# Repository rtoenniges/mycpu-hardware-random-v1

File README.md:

# MyCPU_HDW_RandomV1
A hardware random number generator for the [MyCPU](http://www.mycpu.eu/) based on the work of [Aaron Logue](http://www.cryogenius.com/hardware/rng/).

## Applications
* Games
* Math programs
* Encryption

## Features
* Address selectable through jumpers
* Two independent noise generators
* Both noise generators were adjustable through trimmers (For justage please use this [software](/hist_prg))
* Generates 2x 16bit random numbers simultaneously
* Fetch frequenz about 1MHz (means a new random number every ~16µs)

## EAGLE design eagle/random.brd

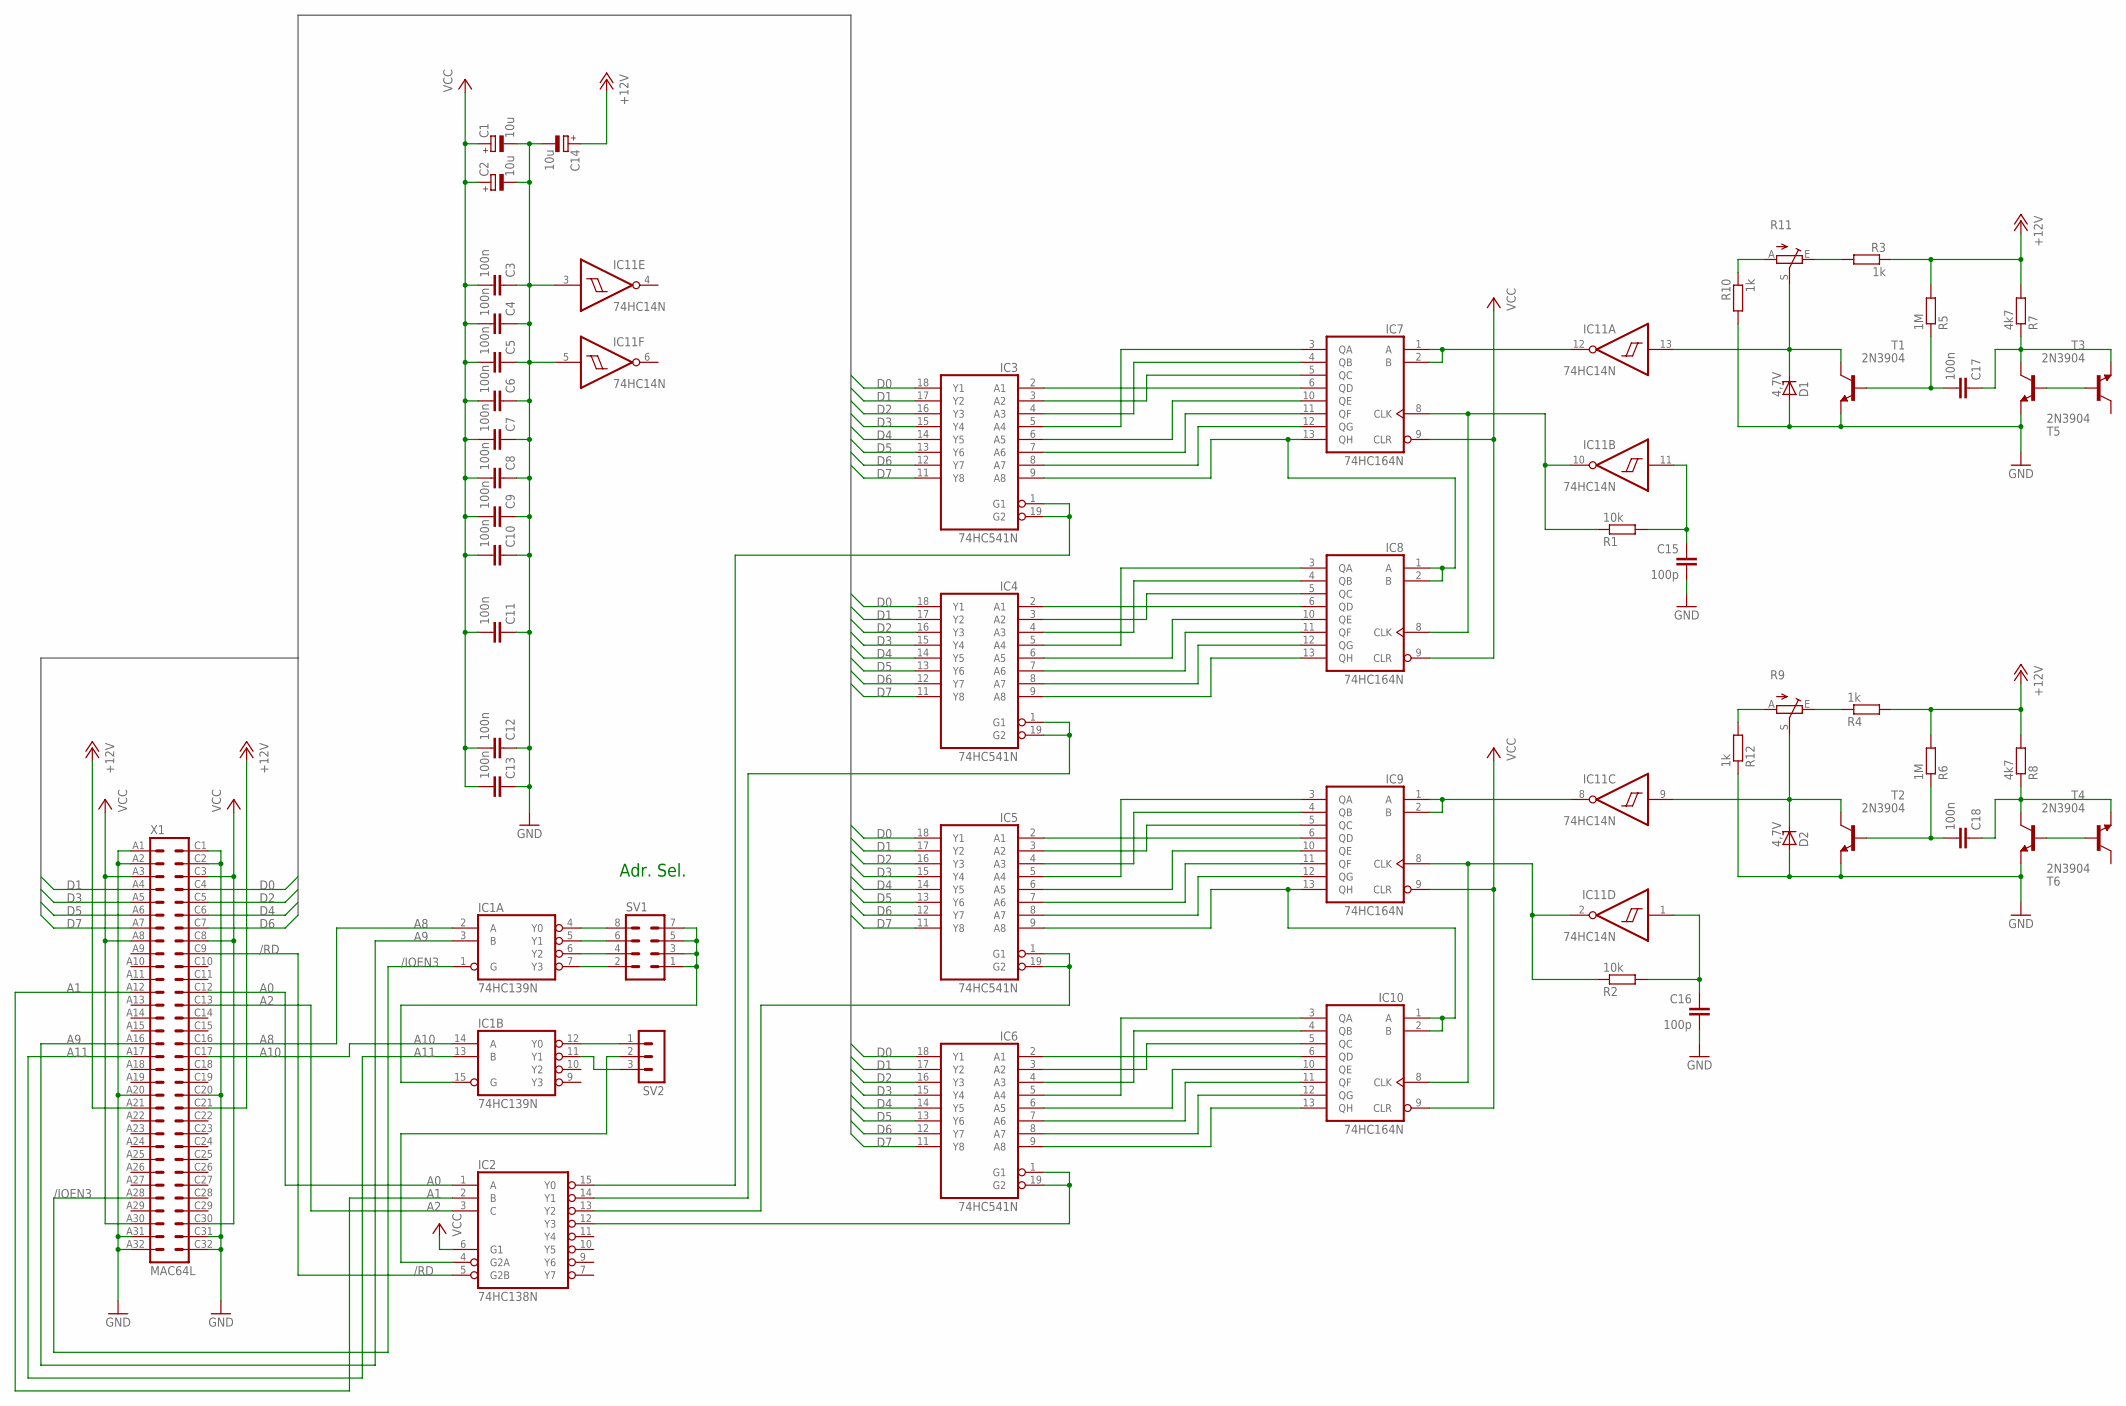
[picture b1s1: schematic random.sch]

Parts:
C1, C2, C14: 10u; TT2D4
C3, C4, C5, C6, C7, C8, C9, C10, C11, C12, C13, C17, C18: 100n; C025-024X044
C15, C16: 100p; C025-024X044
D1, D2: 4,7V; ZDIO-7.5
IC1: 74HC139N; DIL16
IC2: 74HC138N; DIL16
IC3, IC4, IC5, IC6: 74HC541N; DIL20
IC7, IC8, IC9, IC10: 74HC164N; DIL14
IC11: 74HC14N; DIL14
R1, R2: 10k; 0204/7
R3, R4, R10, R12: 1k; 0204/7
R5, R6: 1M; 0204/7
R7, R8: 4k7; 0204/7
R9, R11: TRIM_EU-S63X; S63X
SV1: MA04-2
SV2: MA03-1
T1, T2, T3, T4, T5, T6: 2N3904; TO92
X1: MAC64L

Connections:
+12V: C14.+, R3.1, R4.2, R5.2, R6.2, R7.2, R8.2, X1.A21, X1.C21
/IOEN3: IC1.1 (G), X1.A28
/RD: IC2.5 (G2B), X1.C9
A0: IC2.1 (A), X1.C12
A1: IC2.2 (B), X1.A12
A2: IC2.3 (C), X1.C13
A8: IC1.2 (A), X1.C16
A9: IC1.3 (B), X1.A16
A10: IC1.14 (A), X1.C17
A11: IC1.13 (B), X1.A17
D0: IC3.18 (Y1), IC4.18 (Y1), IC5.18 (Y1), IC6.18 (Y1), X1.C4
D1: IC3.17 (Y2), IC4.17 (Y2), IC5.17 (Y2), IC6.17 (Y2), X1.A4
D2: IC3.16 (Y3), IC4.16 (Y3), IC5.16 (Y3), IC6.16 (Y3), X1.C5
D3: IC3.15 (Y4), IC4.15 (Y4), IC5.15 (Y4), IC6.15 (Y4), X1.A5
D4: IC3.14 (Y5), IC4.14 (Y5), IC5.14 (Y5), IC6.14 (Y5), X1.C6
D5: IC3.13 (Y6), IC4.13 (Y6), IC5.13 (Y6), IC6.13 (Y6), X1.A6
D6: IC3.12 (Y7), IC4.12 (Y7), IC5.12 (Y7), IC6.12 (Y7), X1.C7
D7: IC3.11 (Y8), IC4.11 (Y8), IC5.11 (Y8), IC6.11 (Y8), X1.A7
GND: C1.-, C2.-, C3.1, C4.1, C5.1, C6.1, C7.1, C8.1, C9.1, C10.1, C11.1, C12.1, C13.1, C14.-, C15.2, C16.2, D1.A, D2.A, IC1.8 (GND), IC2.8 (GND), IC3.10 (GND), IC4.10 (GND), IC5.10 (GND), IC6.10 (GND), IC7.7 (GND), IC8.7 (GND), IC9.7 (GND), IC10.7 (GND), IC11.3 (I), IC11.5 (I), IC11.7 (GND), R10.2, R12.1, T1.3 (E), T2.3 (E), T3.3 (E), T4.3 (E), X1.A1, X1.A2, X1.A20, X1.A31, X1.A32, X1.C1, X1.C2, X1.C20, X1.C31, X1.C32
unnamed: T3.2 (B), T5.2 (B)
unnamed: C17.1, R7.1, T3.1 (C), T5.3 (E)
unnamed: C17.2, R5.1, T1.2 (B)
unnamed: D1.C, IC11.13 (I), R11.S, T1.1 (C)
unnamed: T4.2 (B), T6.2 (B)
unnamed: C18.1, R8.1, T4.1 (C), T6.3 (E)
unnamed: C18.2, R6.1, T2.2 (B)
unnamed: D2.C, IC11.9 (I), R9.S, T2.1 (C)
unnamed: C16.1, IC11.1 (I), R2.2
unnamed: IC7.8 (CLK), IC8.8 (CLK), IC11.10 (O), R1.1
unnamed: C15.1, IC11.11 (I), R1.2
unnamed: IC9.1 (A), IC9.2 (B), IC11.8 (O)
unnamed: IC5.9 (A8), IC9.13 (QH), IC10.1 (A), IC10.2 (B)
unnamed: R3.2, R11.E
unnamed: R10.1, R11.A
unnamed: R4.1, R9.E
unnamed: R9.A, R12.2
unnamed: IC5.2 (A1), IC9.6 (QD)
unnamed: IC5.3 (A2), IC9.5 (QC)
unnamed: IC7.1 (A), IC7.2 (B), IC11.12 (O)
unnamed: IC3.9 (A8), IC7.13 (QH), IC8.1 (A), IC8.2 (B)
unnamed: IC5.4 (A3), IC9.4 (QB)
unnamed: IC3.8 (A7), IC7.12 (QG)
unnamed: IC3.7 (A6), IC7.11 (QF)
unnamed: IC3.6 (A5), IC7.10 (QE)
unnamed: IC3.2 (A1), IC7.6 (QD)
unnamed: IC3.3 (A2), IC7.5 (QC)
unnamed: IC3.4 (A3), IC7.4 (QB)
unnamed: IC4.2 (A1), IC8.6 (QD)
unnamed: IC4.3 (A2), IC8.5 (QC)
unnamed: IC4.4 (A3), IC8.4 (QB)
unnamed: IC4.5 (A4), IC8.3 (QA)
unnamed: IC4.6 (A5), IC8.10 (QE)
unnamed: IC4.7 (A6), IC8.11 (QF)
unnamed: IC4.8 (A7), IC8.12 (QG)
unnamed: IC4.9 (A8), IC8.13 (QH)
unnamed: IC5.5 (A4), IC9.3 (QA)
unnamed: IC5.6 (A5), IC9.10 (QE)
unnamed: IC9.8 (CLK), IC10.8 (CLK), IC11.2 (O), R2.1
unnamed: IC5.7 (A6), IC9.11 (QF)
unnamed: IC5.8 (A7), IC9.12 (QG)
unnamed: IC6.2 (A1), IC10.6 (QD)
unnamed: IC6.3 (A2), IC10.5 (QC)
unnamed: IC6.4 (A3), IC10.4 (QB)
unnamed: IC6.5 (A4), IC10.3 (QA)
unnamed: IC6.6 (A5), IC10.10 (QE)
unnamed: IC6.7 (A6), IC10.11 (QF)
unnamed: IC6.8 (A7), IC10.12 (QG)
unnamed: IC6.9 (A8), IC10.13 (QH)
unnamed: IC1.15 (G), SV1.1, SV1.3, SV1.5, SV1.7
unnamed: IC1.4 (Y0), SV1.8
unnamed: IC1.5 (Y1), SV1.6
unnamed: IC1.6 (Y2), SV1.4
unnamed: IC1.7 (Y3), SV1.2
unnamed: IC1.12 (Y0), SV2.1
unnamed: IC1.11 (Y1), SV2.3
unnamed: IC2.4 (G2A), SV2.2
unnamed: IC2.15 (Y0), IC3.1 (G1), IC3.19 (G2)
unnamed: IC2.14 (Y1), IC4.1 (G1), IC4.19 (G2)
unnamed: IC2.13 (Y2), IC5.1 (G1), IC5.19 (G2)
unnamed: IC2.12 (Y3), IC6.1 (G1), IC6.19 (G2)
unnamed: IC3.5 (A4), IC7.3 (QA)
VCC: C1.+, C2.+, C3.2, C4.2, C5.2, C6.2, C7.2, C8.2, C9.2, C10.2, C11.2, C12.2, C13.2, IC1.16 (VCC), IC2.6 (G1), IC2.16 (VCC), IC3.20 (VCC), IC4.20 (VCC), IC5.20 (VCC), IC6.20 (VCC), IC7.9 (CLR), IC7.14 (VCC), IC8.9 (CLR), IC8.14 (VCC), IC9.9 (CLR), IC9.14 (VCC), IC10.9 (CLR), IC10.14 (VCC), IC11.14 (VCC), X1.A3, X1.A8, X1.A30, X1.C3, X1.C8, X1.C30

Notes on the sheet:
Adr. Sel.

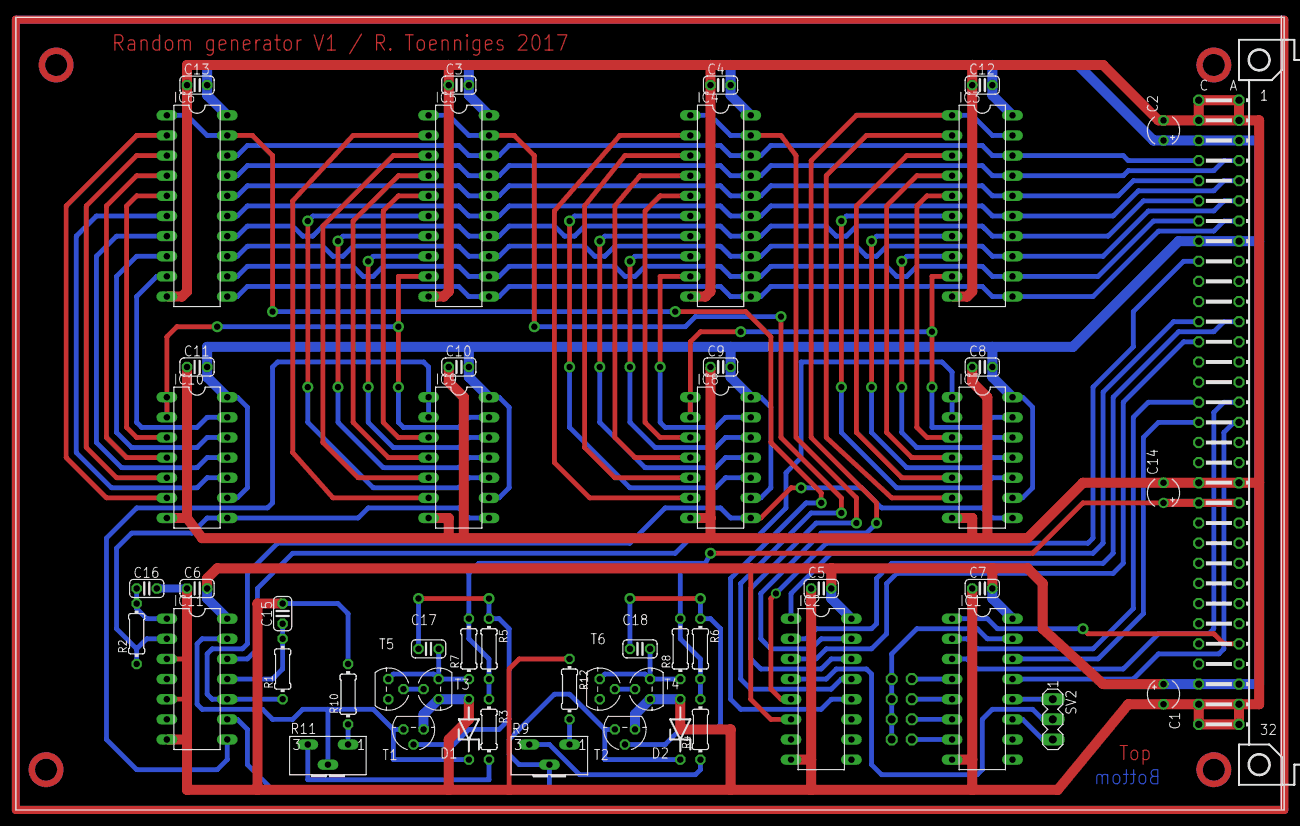
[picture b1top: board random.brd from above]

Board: 2 copper layers, 160.0 x 100.2 mm, 52 parts (1 on the bottom side), 82 nets.

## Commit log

2017-03-20 Initial upload
2017-03-20 Remove files
2017-03-20 Updated layout
2017-03-21 Software update
    spelling mistake :-)
2017-03-21 Spelling
